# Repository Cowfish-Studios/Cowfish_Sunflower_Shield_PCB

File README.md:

Cowfish Studios Sunflower Shield
==============

[*Cowfish Studios Sunflower Shield*](http://kck.st/2NdfVJ6)

The Sunflower Shield allows makers to add a 3.5" (QVGA) TFT LCD Display with capacitive touch to their Arduino projects.

Repository Contents
-------------------

* **/Hardware** - Eagle design files (.brd, .sch)

Documentation
--------------

* **[Hookup Guide](https://www.cowfishstudios.com/learn1/sunflower-shield-35-hmi-display-w-cap-touch-for-arduino)** - Basic hookup guide for the Sunflower Shield.

License Information
-------------------

This product is _**open source**_! 

Please review the LICENSE.md file for license information. 

If you have any questions or concerns on licensing, please contact support@cowfishstudios.com.

Distributed as-is; no warranty is given.

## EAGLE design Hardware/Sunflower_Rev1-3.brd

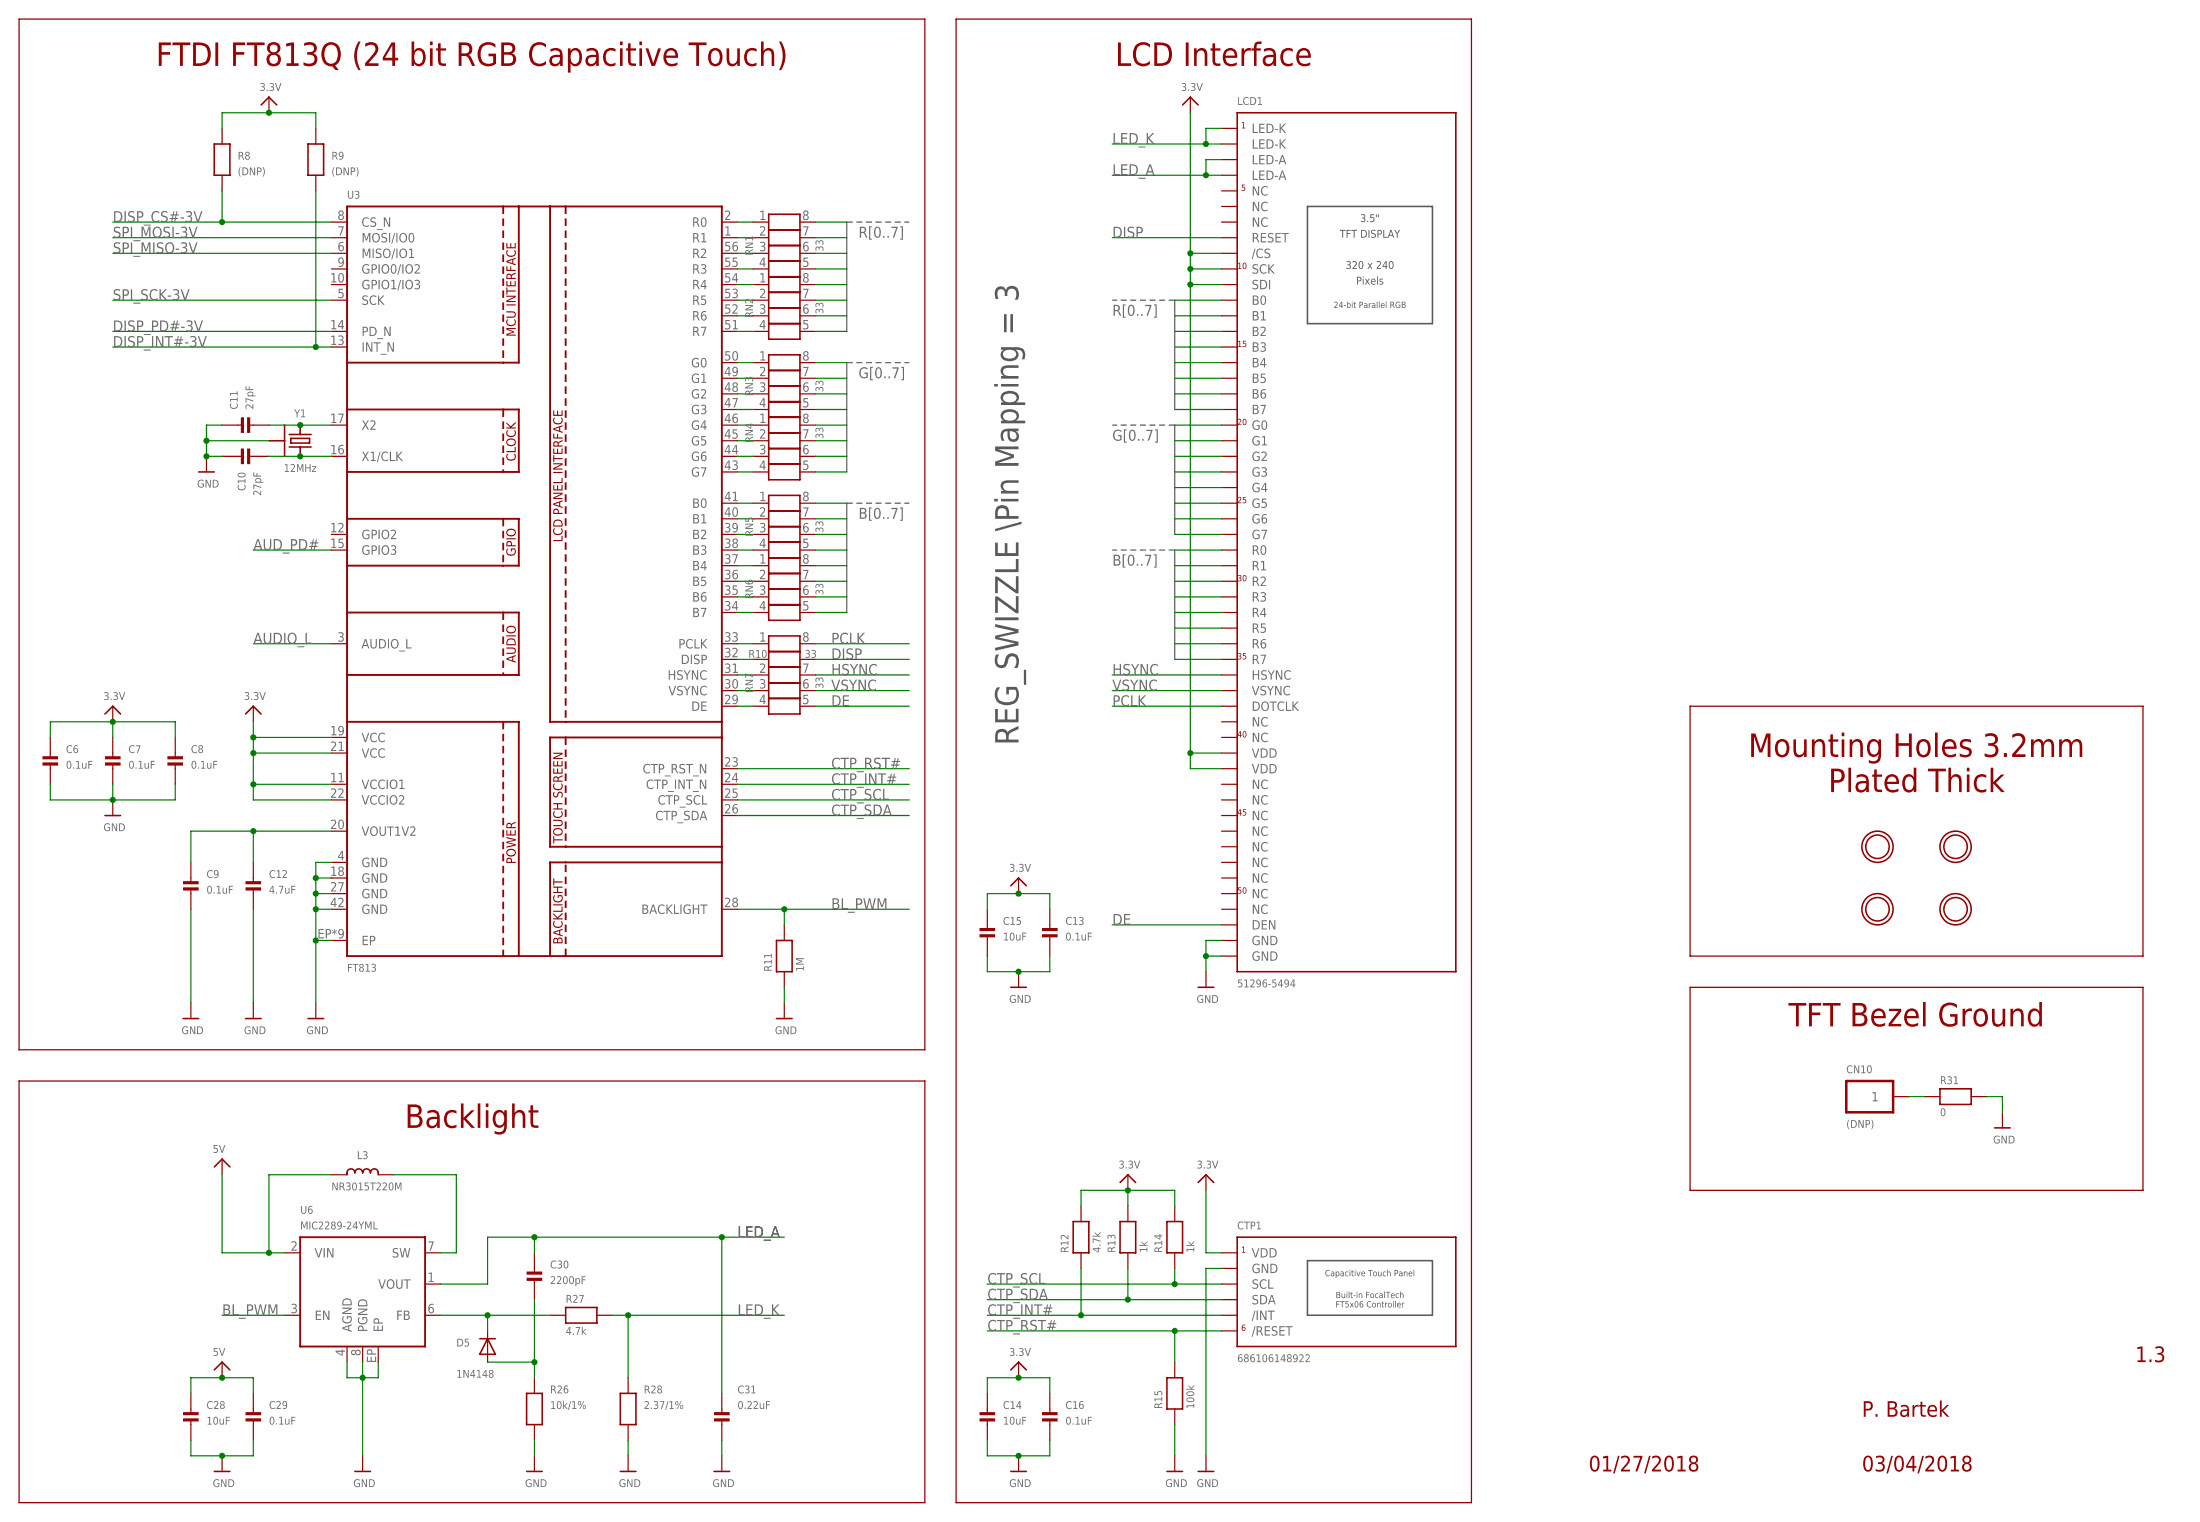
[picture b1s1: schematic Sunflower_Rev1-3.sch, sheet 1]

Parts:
C6, C7, C8, C9, C13, C16, C29: 0.1uF; 0603
C10, C11: 27pF; 0603
C12: 4.7uF; 0603
C14, C15, C28: 10uF; 0603
C30: 2200pF; 0603
C31: 0.22uF; 0603
CN10: (DNP); S7081-42R
CTP1: 686106148922; FPC_686106148922
D5: 1N4148; SOD-323
H1, H2, H3, H4: MOUNTINGHOLE3.2; MOUNTINGHOLE_3.2_PLATED
L3: NR3015T220M; INDUCTOR_3X3MM_TY_NR
LCD1: 51296-5494; FPC_51296_5494
R8, R9: (DNP); 0603
R10: 33; 0603
R11: 1M; 0603
R12, R27: 4.7k; 0603
R13, R14: 1k; 0603
R15: 100k; 0603
R26: 10k/1%; 0603
R28: 2.37/1%; 0805
R31: 0; 0603
RN1, RN2, RN3, RN4, RN5, RN6, RN7: 33; 741-8
U3: FT813; VQFN-56PIN
U6: MIC2289-24YML; MLF-8PIN
Y1: 12MHz; CRYSTAL_3.2X2.5

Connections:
3.3V: C6.1, C7.1, C8.1, C13.1, C14.1, C15.1, C16.1, CTP1.1 (VDD), LCD1.P$9 (/CS), LCD1.P$10 (SCK), LCD1.P$11 (SDI), LCD1.P$41 (VDD), LCD1.P$42 (VDD), R8.2, R9.2, R12.2, R13.2, R14.2, U3.11 (VCCIO1), U3.19 (VCC), U3.21 (VCC), U3.22 (VCCIO2); also elsewhere on the board
5V: C28.1, C29.1, L3.P$1 (1), U6.2 (VIN); also elsewhere on the board
AUDIO_L: U3.3 (AUDIO_L); also elsewhere on the board
AUD_PD#: U3.15 (GPIO3); also elsewhere on the board
B0: LCD1.P$28 (R0), RN5.8 (2)
B1: LCD1.P$29 (R1), RN5.7 (2)
B2: LCD1.P$30 (R2), RN5.6 (2)
B3: LCD1.P$31 (R3), RN5.5 (2)
B4: LCD1.P$32 (R4), RN6.8 (2)
B5: LCD1.P$33 (R5), RN6.7 (2)
B6: LCD1.P$34 (R6), RN6.6 (2)
B7: LCD1.P$35 (R7), RN6.5 (2)
BL_PWM: R11.2, U3.28 (BACKLIGHT), U6.3 (EN)
CTP_INT#: CTP1.5 (/INT), R12.1, U3.24 (CTP_INT_N)
CTP_RST#: CTP1.6 (/RESET), R15.2, U3.23 (CTP_RST_N)
CTP_SCL: CTP1.3 (SCL), R14.1, U3.25 (CTP_SCL)
CTP_SDA: CTP1.4 (SDA), R13.1, U3.26 (CTP_SDA)
DE: LCD1.P$52 (DEN), RN7.5 (2)
DISP: LCD1.P$8 (RESET), R10.2
DISP_CS#-3V: R8.1, U3.8 (CS_N); also elsewhere on the board
DISP_INT#-3V: R9.1, U3.13 (INT_N); also elsewhere on the board
DISP_PD#-3V: U3.14 (PD_N); also elsewhere on the board
G0: LCD1.P$20 (G0), RN3.8 (2)
G1: LCD1.P$21 (G1), RN3.7 (2)
G2: LCD1.P$22 (G2), RN3.6 (2)
G3: LCD1.P$23 (G3), RN3.5 (2)
G4: LCD1.P$24 (G4), RN4.8 (2)
G5: LCD1.P$25 (G5), RN4.7 (2)
G6: LCD1.P$26 (G6), RN4.6 (2)
G7: LCD1.P$27 (G7), RN4.5 (2)
GND: C6.2, C7.2, C8.2, C9.2, C10.2, C11.1, C12.2, C13.2, C14.2, C15.2, C16.2, C28.2, C29.2, C31.2, CTP1.2 (GND), CTP1.SUPPORT1 (GND), CTP1.SUPPORT2 (GND), LCD1.P$53 (GND), LCD1.P$54 (GND), LCD1.SUPPORT1 (GND), LCD1.SUPPORT2 (GND), R11.1, R15.1, R26.1, R28.1, R31.2, U3.4 (GND), U3.18 (GND), U3.27 (GND), U3.42 (GND), U3.EP, U3.TV@1 (EP), U3.TV@2 (EP), U3.TV@3 (EP), U3.TV@4 (EP), U3.TV@5 (EP), U3.TV@6 (EP), U3.TV@7 (EP), U3.TV@8 (EP), U6.4 (AGND), U6.8 (PGND), U6.EP, Y1.GND1 (3), Y1.GND2 (3); also elsewhere on the board
HSYNC: LCD1.P$36 (HSYNC), RN7.7 (2)
LED_A: C30.1, C31.1, LCD1.P$3 (LED-A), LCD1.P$4 (LED-A), U6.1 (VOUT)
LED_K: LCD1.P$1 (LED-K), LCD1.P$2 (LED-K), R27.2, R28.2
unnamed: RN1.1, U3.2 (R0)
unnamed: RN1.2 (1), U3.1 (R1)
unnamed: RN1.3 (1), U3.56 (R2)
unnamed: RN1.4 (1), U3.55 (R3)
unnamed: RN2.1, U3.54 (R4)
unnamed: RN2.2 (1), U3.53 (R5)
unnamed: RN2.3 (1), U3.52 (R6)
unnamed: RN2.4 (1), U3.51 (R7)
unnamed: RN3.1, U3.50 (G0)
unnamed: RN3.2 (1), U3.49 (G1)
unnamed: RN3.3 (1), U3.48 (G2)
unnamed: RN3.4 (1), U3.47 (G3)
unnamed: RN4.1, U3.46 (G4)
unnamed: RN4.2 (1), U3.45 (G5)
unnamed: RN4.3 (1), U3.44 (G6)
unnamed: RN4.4 (1), U3.43 (G7)
unnamed: RN5.1, U3.41 (B0)
unnamed: RN5.2 (1), U3.40 (B1)
unnamed: RN5.3 (1), U3.39 (B2)
unnamed: RN5.4 (1), U3.38 (B3)
unnamed: RN6.1, U3.37 (B4)
unnamed: RN6.2 (1), U3.36 (B5)
unnamed: RN6.3 (1), U3.35 (B6)
unnamed: RN6.4 (1), U3.34 (B7)
unnamed: RN7.1, U3.33 (PCLK)
unnamed: RN7.2 (1), U3.31 (HSYNC)
unnamed: RN7.3 (1), U3.30 (VSYNC)
unnamed: RN7.4 (1), U3.29 (DE)
unnamed: CN10.P$1, R31.1
unnamed: C11.2, U3.17 (X2), Y1.2
unnamed: C9.1, C12.1, U3.20 (VOUT1V2)
unnamed: C10.1, U3.16 (X1/CLK), Y1.1
unnamed: L3.P$2 (2), U6.7 (SW)
unnamed: D5.C, R27.1, U6.6 (FB)
unnamed: C30.2, D5.A, R26.2
unnamed: R10.1, U3.32 (DISP)
PCLK: LCD1.P$38 (DOTCLK), RN7.8 (2)
R0: LCD1.P$12 (B0), RN1.8 (2)
R1: LCD1.P$13 (B1), RN1.7 (2)
R2: LCD1.P$14 (B2), RN1.6 (2)
R3: LCD1.P$15 (B3), RN1.5 (2)
R4: LCD1.P$16 (B4), RN2.8 (2)
R5: LCD1.P$17 (B5), RN2.7 (2)
R6: LCD1.P$18 (B6), RN2.6 (2)
R7: LCD1.P$19 (B7), RN2.5 (2)
SPI_MISO-3V: U3.6 (MISO/IO1); also elsewhere on the board
SPI_MOSI-3V: U3.7 (MOSI/IO0); also elsewhere on the board
SPI_SCK-3V: U3.5 (SCK); also elsewhere on the board
VSYNC: LCD1.P$37 (VSYNC), RN7.6 (2)

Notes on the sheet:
REG_SWIZZLE \Pin Mapping = 3
LCD Interface
Backlight
FTDI FT813Q (24 bit RGB Capacitive Touch)
Mounting Holes 3.2mm Plated Thick
RN1
RN2
RN3
RN4
RN5
RN6
RN7
TFT Bezel Ground
P. Bartek
1.3
01/27/2018
03/04/2018

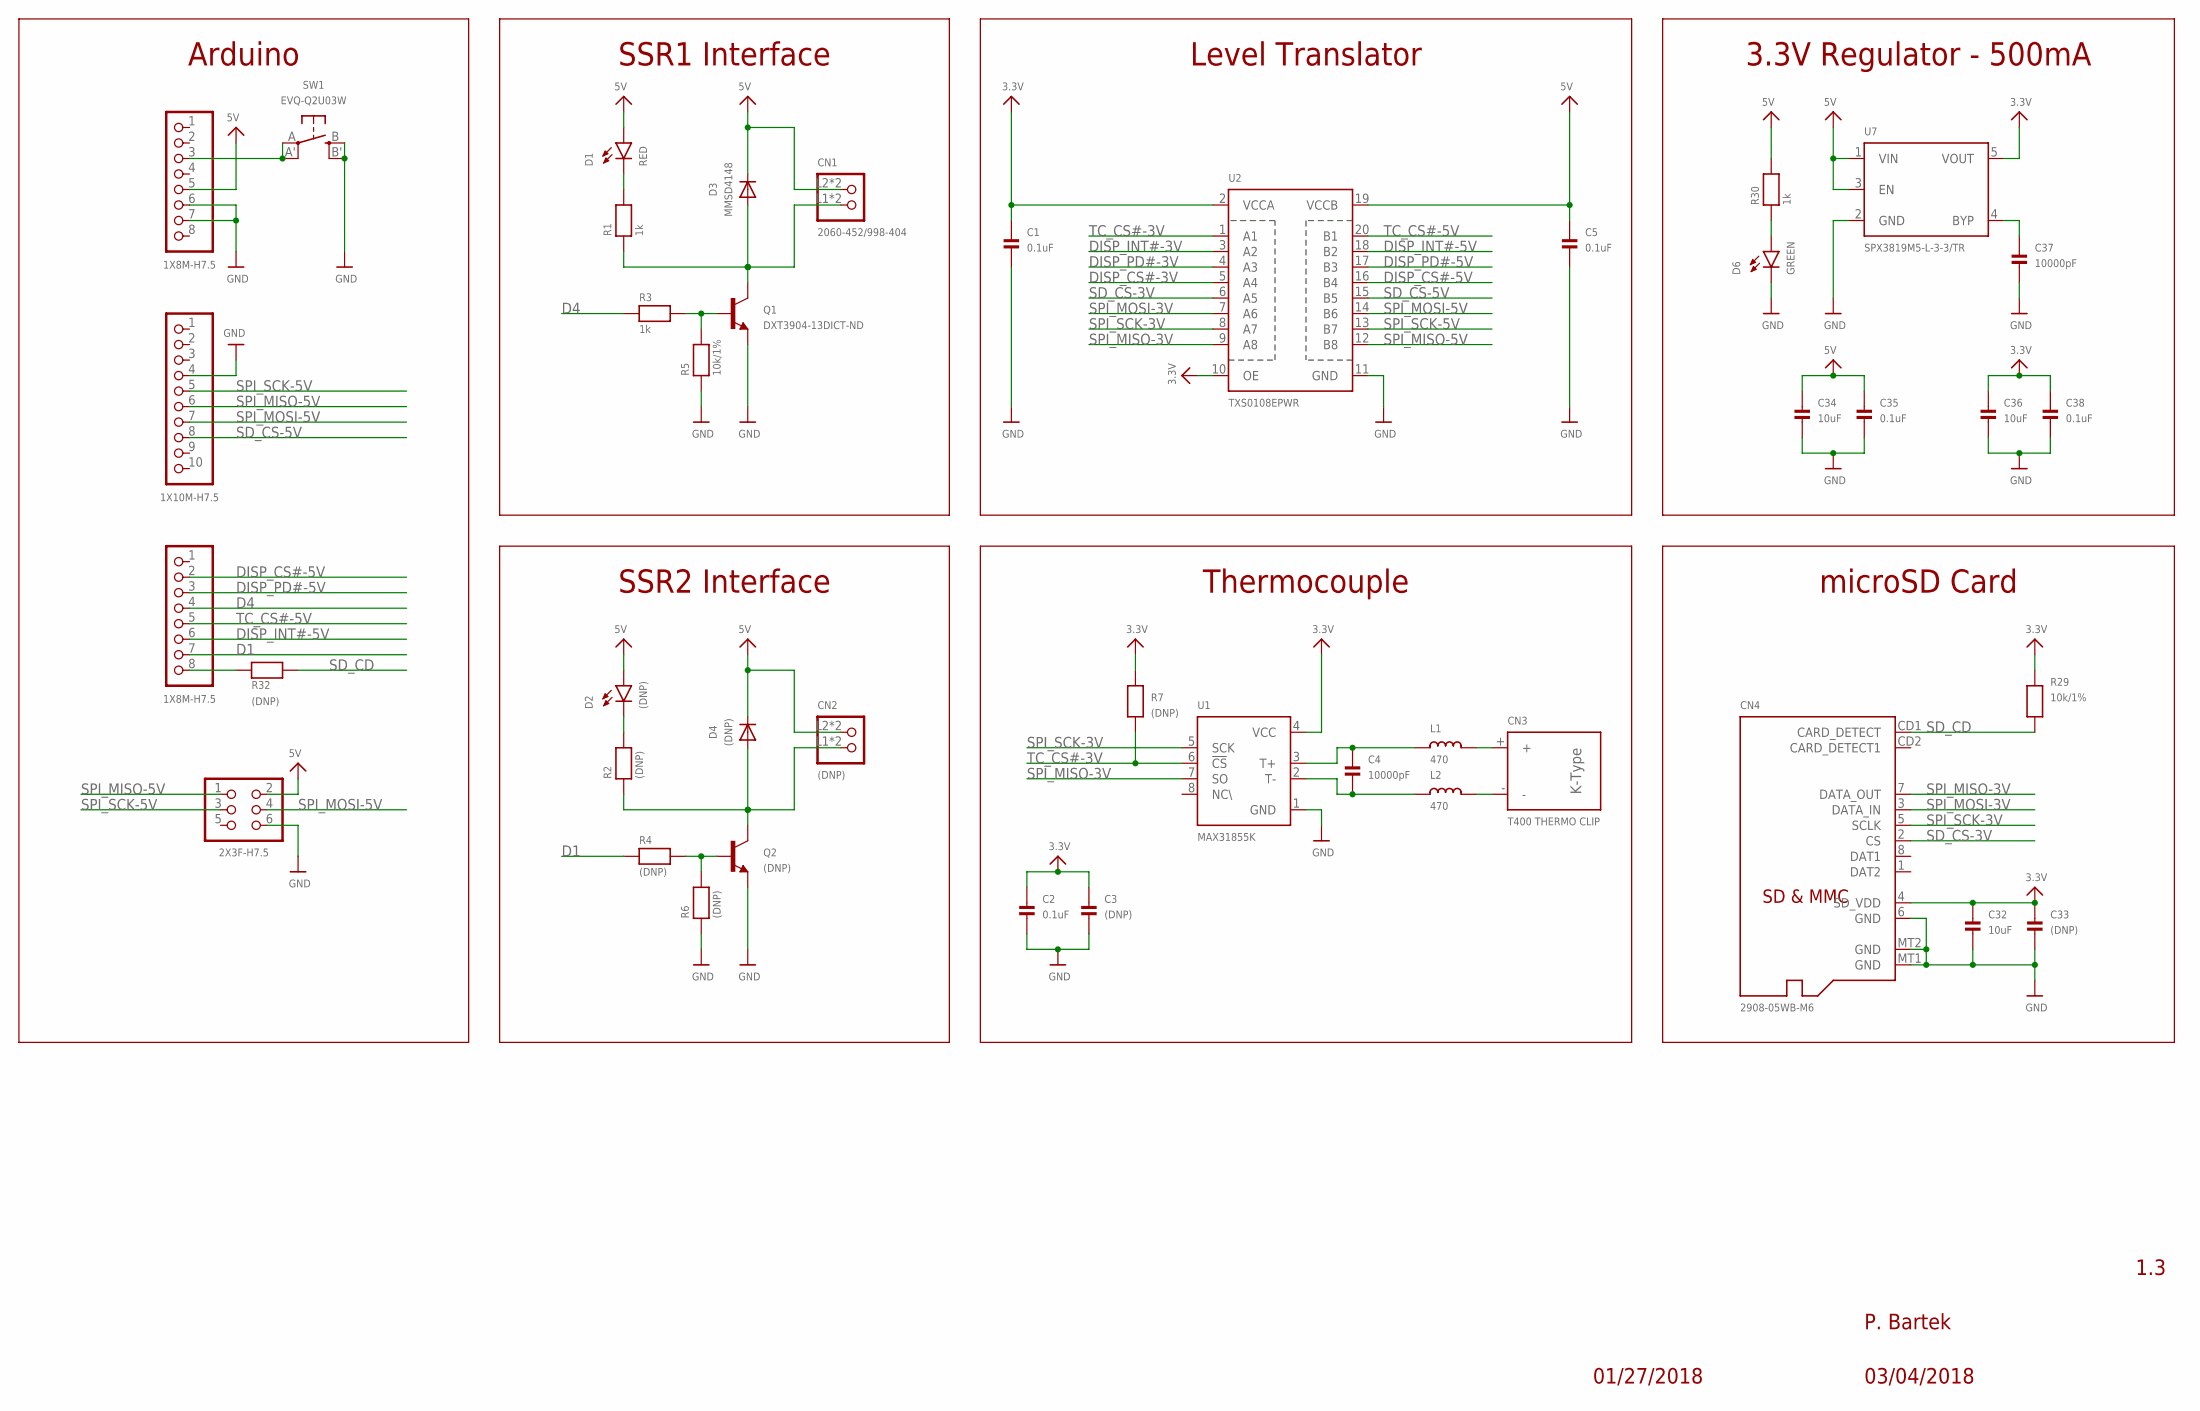
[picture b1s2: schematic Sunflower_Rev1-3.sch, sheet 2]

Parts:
C1, C2, C5, C35, C38: 0.1uF; 0603
C3, C33: (DNP); 0603
C4, C37: 10000pF; 0603
C32, C34, C36: 10uF; 0603
CN1: 2060-452/998-404; P-2060-452/998-404
CN2: (DNP); P-2060-452/998-404
CN3: T400 THERMO CLIP; THERMOCOUPLE_CLIP_INSIDE
CN4: 2908-05WB-M6; MICROSD
CN6, CN8: 1X8M-H7.5; 1X08_SMD_M_LEYCONN
CN7: 1X10M-H7.5; 1X10_SMD_M_LEYCONN
CN9: 2X3F-H7.5; 2X3_SMD_F_LEYCONN
D1: RED; LED-0603
D2: (DNP); LED-0603
D3: MMSD4148; SOD-123
D4: (DNP); SOD-123
D6: GREEN; LED-0603
L1, L2: 470; 0603
Q1: DXT3904-13DICT-ND; SOT-89-3
Q2: (DNP); SOT-89-3
R1, R3, R30: 1k; 0603
R2, R4, R6, R7, R32: (DNP); 0603
R5, R29: 10k/1%; 0603
SW1: EVQ-Q2U03W; EVQ-Q2
U1: MAX31855K; SOIC8
U2: TXS0108EPWR; TSSOP-20PIN
U7: SPX3819M5-L-3-3/TR; SOT23-5PIN

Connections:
3.3V: C1.1, C2.1, C3.1, C32.1, C33.1, C36.1, C38.1, CN4.4 (SD_VDD), R7.2, R29.2, U1.4 (VCC), U2.2 (VCCA), U2.10 (OE), U7.5 (VOUT); also elsewhere on the board
5V: C5.1, C34.1, C35.1, CN1.L2 (P1.1), CN1.L2.2 (P1.1), CN2.L2 (P1.1), CN2.L2.2 (P1.1), CN6.5, CN9.2, D1.A, D2.A, D3.C, D4.C, R30.2, U2.19 (VCCB), U7.1 (VIN), U7.3 (EN); also elsewhere on the board
D1: CN8.7, R4.1
D4: CN8.4, R3.1
DISP_CS#-3V: U2.5 (A4); also elsewhere on the board
DISP_CS#-5V: CN8.2, U2.16 (B4)
DISP_INT#-3V: U2.3 (A2); also elsewhere on the board
DISP_INT#-5V: CN8.6, U2.18 (B2)
DISP_PD#-3V: U2.4 (A3); also elsewhere on the board
DISP_PD#-5V: CN8.3, U2.17 (B3)
GND: C1.2, C2.2, C3.2, C5.2, C32.2, C33.2, C34.2, C35.2, C36.2, C37.2, C38.2, CN4.6 (GND), CN4.MT1 (GND), CN4.MT2 (GND), CN6.6, CN6.7, CN7.4, CN9.6, D6.C, Q1.E, Q2.E, R5.1, R6.1, SW1.B (S), SW1.B' (S1), U1.1 (GND), U2.11 (GND), U7.2 (GND); also elsewhere on the board
unnamed: D6.A, R30.1
unnamed: C4.1, L1.1, U1.3 (T+)
unnamed: C4.2, L2.1, U1.2 (T-)
unnamed: CN3.+, L1.2
unnamed: CN3.-, L2.2
unnamed: C37.1, U7.4 (BYP)
unnamed: Q1.B, R3.2, R5.2
unnamed: Q2.B, R4.2, R6.2
unnamed: CN1.L1 (P2.1), CN1.L1.2 (P2.1), D3.A, Q1.C, Q1.C@1 (C), R1.1
unnamed: D1.C, R1.2
unnamed: CN8.8, R32.1
unnamed: D2.C, R2.2
unnamed: CN2.L1 (P2.1), CN2.L1.2 (P2.1), D4.A, Q2.C, Q2.C@1 (C), R2.1
unnamed: CN6.3, SW1.A, SW1.A' (P1)
SD_CD: CN4.CD1 (CARD_DETECT), R29.1, R32.2
SD_CS-3V: CN4.2 (CS), U2.6 (A5)
SD_CS-5V: CN7.8, U2.15 (B5)
SPI_MISO-3V: CN4.7 (DATA_OUT), U1.7 (SO), U2.9 (A8); also elsewhere on the board
SPI_MISO-5V: CN7.6, CN9.1, U2.12 (B8)
SPI_MOSI-3V: CN4.3 (DATA_IN), U2.7 (A6); also elsewhere on the board
SPI_MOSI-5V: CN7.7, CN9.4, U2.14 (B6)
SPI_SCK-3V: CN4.5 (SCLK), U1.5 (SCK), U2.8 (A7); also elsewhere on the board
SPI_SCK-5V: CN7.5, CN9.3, U2.13 (B7)
TC_CS#-3V: R7.1, U1.6 (!CS), U2.1 (A1)
TC_CS#-5V: CN8.5, U2.20 (B1)

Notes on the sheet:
3.3V Regulator - 500mA
Thermocouple
Level Translator
microSD Card
Arduino
SSR1 Interface
SSR2 Interface
P. Bartek
1.3
01/27/2018
03/04/2018

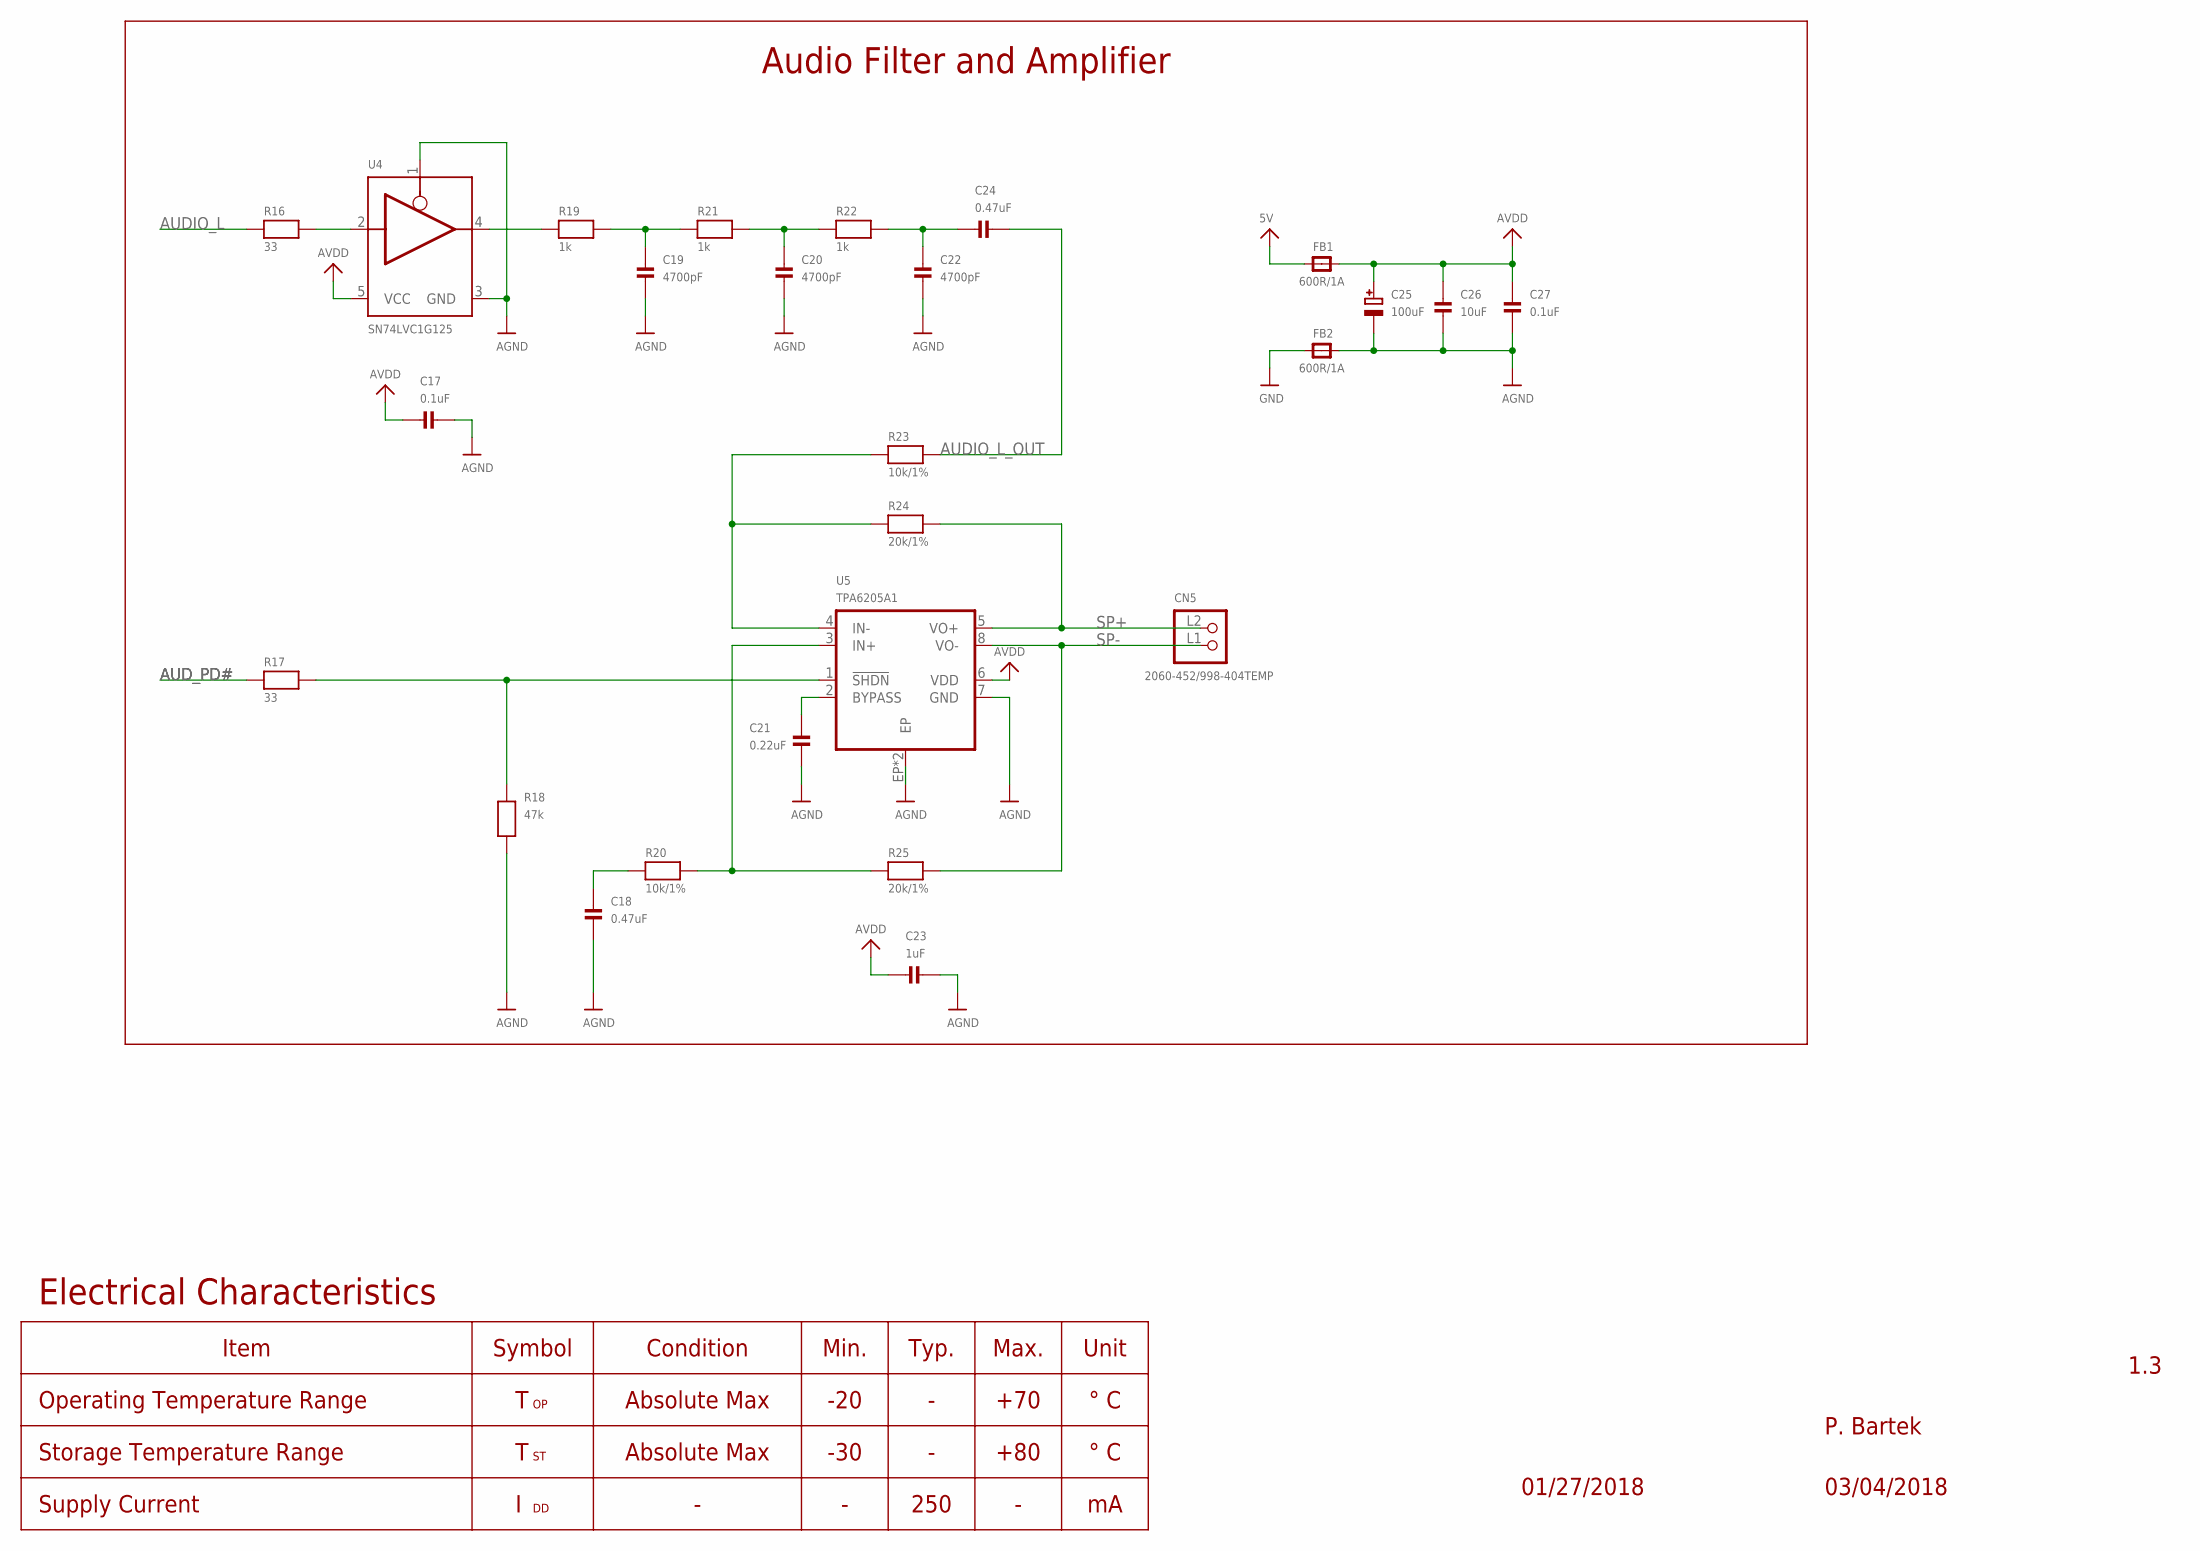
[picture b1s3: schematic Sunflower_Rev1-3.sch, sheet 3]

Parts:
C17, C27: 0.1uF; 0603
C18, C24: 0.47uF; 0603
C19, C20, C22: 4700pF; 0603
C21: 0.22uF; 0805
C23: 1uF; 0603
C25: 100uF; EIA3216-18/A-R
C26: 10uF; 0603
CN5: 2060-452/998-404TEMP; P-2060-452/998-404
FB1, FB2: 600R/1A; 0805
R16, R17: 33; 0603
R18: 47k; 0603
R19, R21, R22: 1k; 0603
R20, R23: 10k/1%; 0603
R24, R25: 20k/1%; 0603
U4: SN74LVC1G125; SOT23-5PIN
U5: TPA6205A1; MSOP-8PIN

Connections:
5V: FB1.1; also elsewhere on the board
AGND: C17.2, C18.2, C19.2, C20.2, C21.2, C22.2, C23.2, C25.-, C26.2, C27.2, FB2.2, R18.1, U4.1 (OE), U4.3 (GND), U5.7 (GND), U5.EP, U5.TV (EP)
AUDIO_L: R16.1; also elsewhere on the board
AUDIO_L_OUT: C24.2, R23.2
AUD_PD#: R17.1; also elsewhere on the board
AVDD: C17.1, C23.1, C25.+, C26.1, C27.1, FB1.2, U4.5 (VCC), U5.6 (VDD)
GND: FB2.1; also elsewhere on the board
unnamed: R16.2, U4.2 (I)
unnamed: R17.2, R18.2, U5.1 (!SHDN)
unnamed: R19.1, U4.4 (O)
unnamed: C19.1, R19.2, R21.1
unnamed: C20.1, R21.2, R22.1
unnamed: C21.1, U5.2 (BYPASS)
unnamed: C22.1, C24.1, R22.2
unnamed: R20.2, R25.1, U5.3 (IN+)
unnamed: C18.1, R20.1
unnamed: R23.1, R24.1, U5.4 (IN-)
SP+: CN5.L2 (P1.1), R24.2, U5.5 (VO+)
SP-: CN5.L1 (P2.1), R25.2, U5.8 (VO-)

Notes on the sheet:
Audio Filter and Amplifier
Electrical Characteristics
Operating Temperature Range
Item
Storage Temperature Range
Supply Current
Symbol
Condition
Absolute Max
Min.
Typ.
Max.
Unit
-20
-30
+70
+80
° C
250
P. Bartek
1.3
01/27/2018
03/04/2018

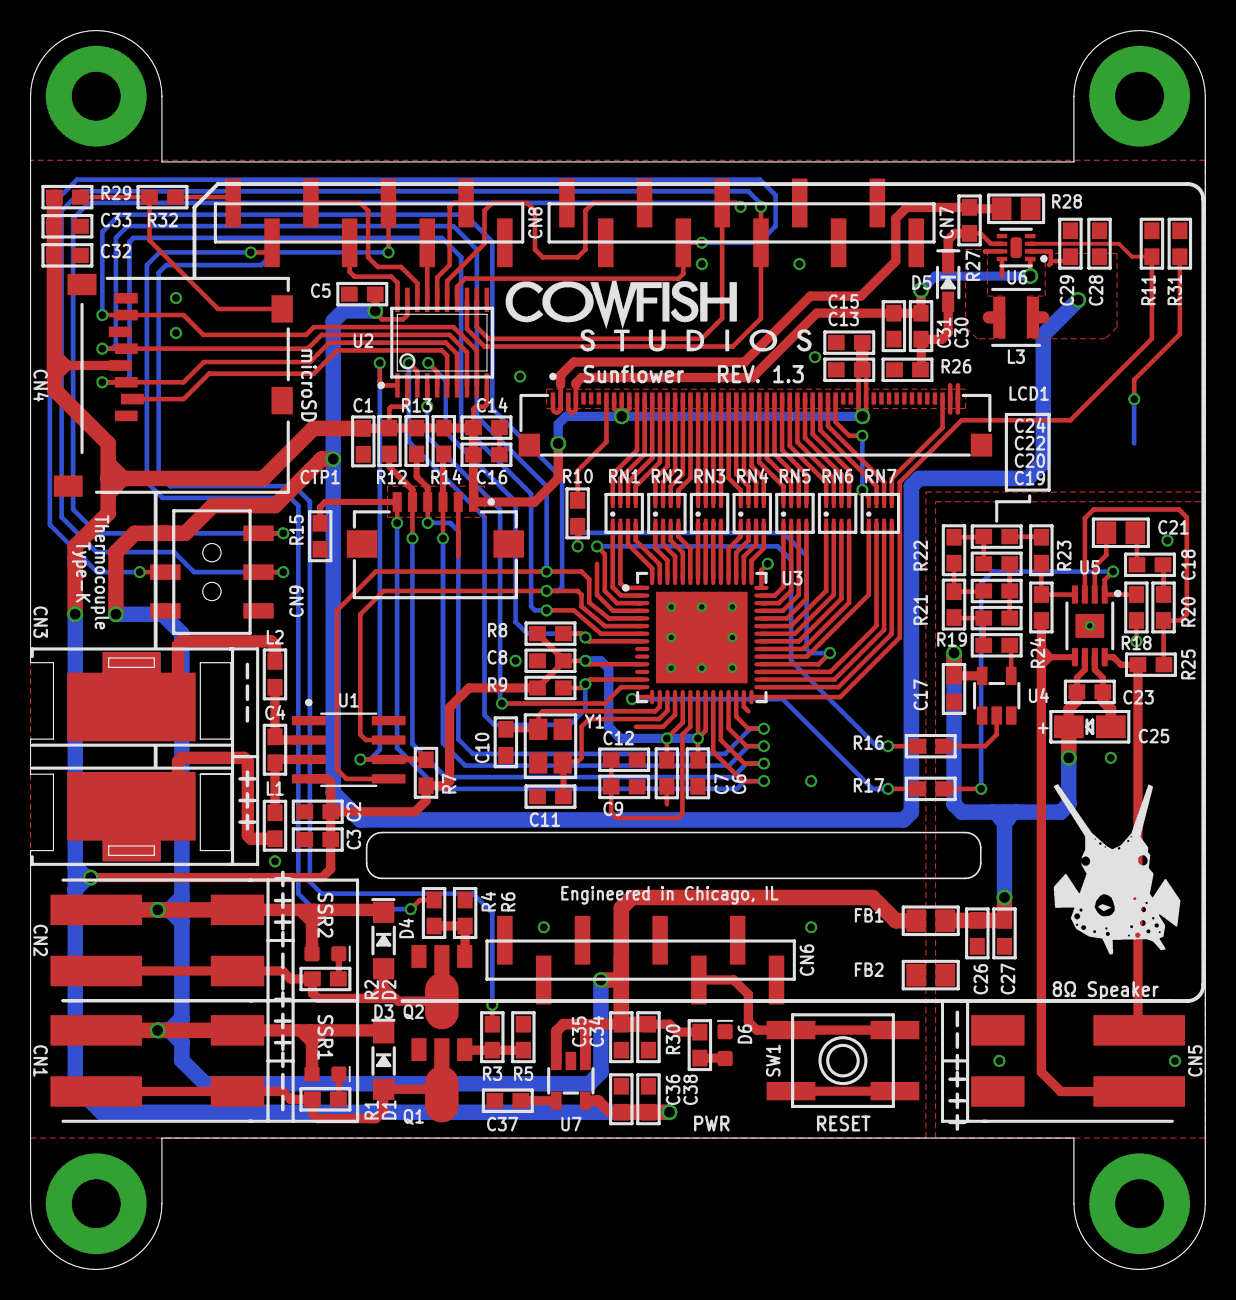
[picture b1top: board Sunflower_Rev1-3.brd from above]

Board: 2 copper layers, 76.8 x 81.0 mm, 115 parts (1 on the bottom side), 125 nets.

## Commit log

2018-08-13 Fix Typo + Add Schematic as PDF
    Schematic Typo Corrected.
    Electrical Characteristic Updated.
    Sunflower Shield PDF Schematic Added.

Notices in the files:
parts and their libraries:
CowFish-Displays: This work is placed in the public domain, and may be freely used for commercial and non-commercial work with the following conditions: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
SparkFun-LED: Licensing: Creative Commons ShareAlike 4.0 International - https://creativecommons.org/licenses/by-sa/4.0
